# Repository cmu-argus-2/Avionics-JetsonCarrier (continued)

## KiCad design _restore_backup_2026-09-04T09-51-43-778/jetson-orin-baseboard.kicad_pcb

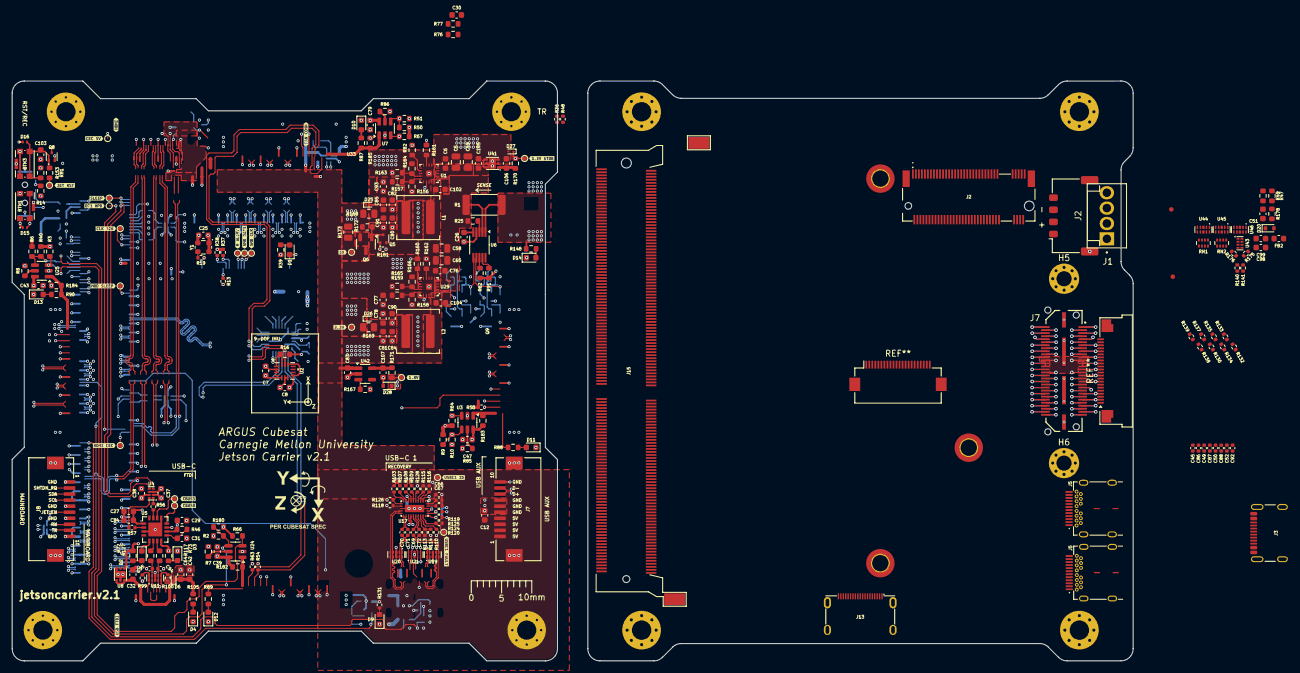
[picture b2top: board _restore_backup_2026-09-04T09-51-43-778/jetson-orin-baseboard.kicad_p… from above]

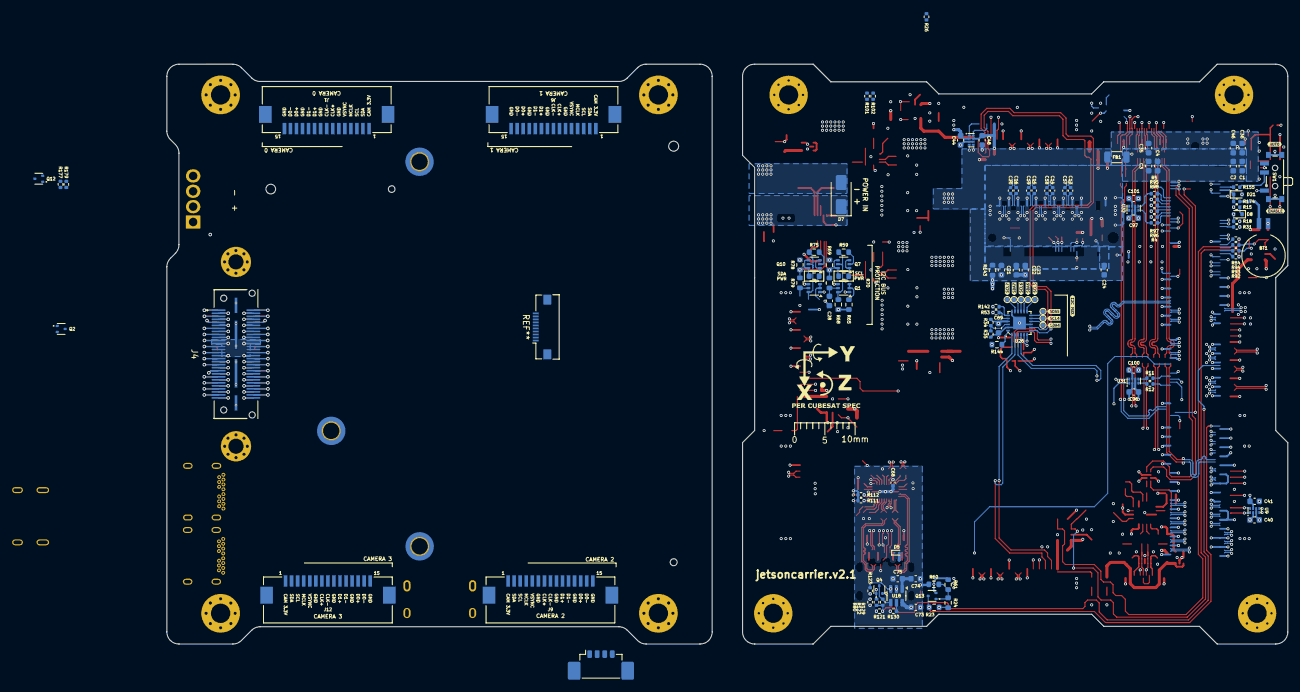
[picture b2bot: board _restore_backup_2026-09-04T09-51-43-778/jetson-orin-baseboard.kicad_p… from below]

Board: 8 copper layers, 90.2 x 95.9 mm, 411 parts (129 on the bottom side), 312 nets.

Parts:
BT1: MS621FE-FL11E
BTN1, BTN3: KMR211NGLFS; SW_Push_1P1T-SH_NO_CK_KMR2xxG
C1, C2, C3, C4, C35, C36, C46, C78, C80, C81, C82, C84, C85, C90, C91: 22uF; C_0603_1608Metric
C5, C58, C59, C65: 22uF; C_0805_2012Metric
C6, C7, C8, C25, C27, C29, C31, C37, C38, C39, C40, C41, C43, C44, C47, C48, C64, C73, C75, C76, C79, C89, C96, C97, C98, C99, C100, C101, C102, C103, C104: 100nF; C_0603_1608Metric
C12, C42, C77, C93, C107: 1uF; C_0603_1608Metric
C13, C14, C15, C16, C17, C18, C19, C20: 220nF; C_0402_1005Metric
C21, C22, C23, C24, C32, C34, C51, C74, C83, C105, C106: 10uF; C_0603_1608Metric
C26: 3300pF; C_0603_1608Metric
C28, C30: 10nF; C_0603_1608Metric
C45, C49, C50, C52, C67, C68, C69, C70, C71, C72, C86, C87, C88, C92: 100nF; C_0402_1005Metric
C66: 10uF; C_0402_1005Metric
C94, C95: 47pF; C_0402_1005Metric
D1, D2, D3, D4, D9, D10, D11, D12, D13, D14: LED_G_0603_LTST-C190GKT; LED_0603_1608Metric
D5, D6, D25: ESD9X5.0ST5G; D_SOD-923
D7: 10V; D_SMA
D8, D20, D21: RB521S30T1G; D_SOD-523
D15, D16: TPD1E0B04; Texas_DPY0002A_0.6x1mm_P0.65mm
D26, D27: ESD9X3.3ST5G; D_SOD-923
D28: ESD1V8WT; D_SOD-523
FB1: 74279221100; L_1206_3216Metric
FB2: BLM21PG221SN1D; L_0603_1608Metric
H1, H2#2, H3#2, H4#2: MountingHole_Pad; MountingHole2
H1#2, H2, H3, H4: MountingHole_Pad; MountingHole_3.2mm_M3_Pad_Via
H5, H6#2: MountingHole_Pad; MountingHole_2.5mm_Pad_Via
H5#2: 9774025151; MountingHole_2.7mm_M2.5_DIN965_Pad_TopBottom
H6, H7: 9774065151; MountingHole_2.7mm_M2.5_DIN965_Pad_TopBottom
J1: 205338-0004; Molex_Pico-Lock_205338-0004_1x04-1MP_P2.00mm_Horizontal
J1#2, J6, J9, J12: 522071560; CON_522071560_MOL
J2: 282834-4; TE_282834-4
J2#2: 1-2199230-6; Bus_M.2_Socket_Key_M_TE_1-2199230-6
J3: USB4105-GF-A; USB_C_Receptacle_GCT_USB4105-xx-A_16P_TopMnt_Horizontal
J4: QTH-030-01-L-D-A; SAMTEC_QSH-030-01-L-D-A
J5, J5#2: 632723300011; USB-C_Receptacle_WE_632723300011
J7, J8: 522711069; CON_522711069_MOL
J7#2: QTH-030-01-L-D-A; SAMTEC-QTH-030-01-L-D-A
J10: 0533980471; Molex_PicoBlade_53398-0471_1x04-1MP_P1.25mm_Vertical
J13: 685119136923; HDMI-Mini-C_Receptacle_WE_685119136923
J15: Bus_DDR4_SODIMM_CUSTOM_Jetson-Orin-H9.2mm-socket; TE_2309413
L1, L2: XGL6030-182MEC; L_Coilcraft_XAL6030-XXX
Q1, Q9: BSS138DWQ-7; SOT-363_SC-70-6
Q2, Q4, Q5, Q8, Q12, Q13: PJE138K; SOT-523
Q6: SSM3J332R; SOT-23-3
Q7, Q10: MBT2222ADW1T1; SOT-363_SC-70-6
R1: 10m; R_2512_6332Metric
R2, R6, R10, R49, R51, R65, R76, R178: 100k; R_0603_1608Metric
R3, R9, R14, R16, R24, R40, R46, R47, R50, R60, R64, R66, R67, R68, R69, R77, R78, R81, R82, R144, R148, R157, R159, R161, R162, R172, R180: 10k; R_0603_1608Metric
R4, R5, R11, R12, R13, R19, R34, R35, R53, R56, R57, R84, R92, R93, R94, R95, R96, R97, R98, R103, R107, R108, R109, R110, R113, R114, R118, R119, R124, R125, R140, R141, R142, R155, R181: 0R; R_0402_1005Metric
R7, R8, R85, R86, R87, R88, R89, R90, R105: 4k7; R_0603_1608Metric
R15: 200R; R_0402_1005Metric
R18, R115, R116, R120, R122, R123, R129: 10k; R_0402_1005Metric
R23, R62, R71, R74, R143, R160, R167, R170, R171, R182, R183, R184, R185: 0R; R_0603_1608Metric
R25: 1k; R_0603_1608Metric
R26, R36, R48, R54, R55, R63, R101, R102, R130, R174, R175, R176, R177, R179: 2k2; R_0402_1005Metric
R31, R80, R126: 200k; R_0402_1005Metric
R37, R38: 47k; R_0402_1005Metric
R39, R72, R73: 3k3; R_0603_1608Metric
R59, R75: 680R; R_0603_1608Metric
R61, R70, R79, R153: 200k; R_0603_1608Metric
R91: 150k; R_0603_1608Metric
R99, R100: 5k1; R_0402_1005Metric
R111, R112, R131: 4k7; R_0402_1005Metric
R117, R127: 27R; R_0603_1608Metric
R121: 1k; R_0402_1005Metric
R128: 887k; R_0402_1005Metric
R132, R133, R134, R135, R136, R137, R138, R139: 499R; R_0402_1005Metric
R156, R158: 220k; R_0603_1608Metric
R163: 110k; R_0603_1608Metric
R164: 15k; R_0603_1608Metric
R165: 90k9; R_0603_1608Metric
R166: 20k; R_0603_1608Metric
R168, R169, R173: 0R; R_0805_2012Metric
RN1, RN2: 4x0R; R_Array_Concave_4x0402
SW1: SW_SPDT; SW_SPDT_PCM12
TP5, TP7, TP8, TP9, TP10, TP11, TP12, TP13, TP14, TP15, TP16, TP17, TP18, TP19, TP20, TP21, TP22, TP23, TP24, TP25, TP26, TP27, TP28, TP29, TP30, TP31: TP_0.75mm_SMD; TP_SMD_0.75mm
U1, U29: TPS56C230; QFN-20-1EP_3x3mm_P0.45mm
U2: BMX160; BMX160_BOS
U3, U7, U18, U24, U25: AP22615A; TSOT-23-6
U4, U9, U31, U32, U33, U43: NTS0102; XSON-8_1x1.95mm_P0.5mm
U5: FT230X; QFN-16-1EP_4x4mm_P0.65mm
U6: ADM1176-1ARMZ-R7; MSOP-10_3x3mm_P0.5mm
U8, U41: NCP730BMT330; WSON-6-1EP_2x2mm_P0.65mm
U11, U19, U20, U21, U44, U45, U46: TPD4E05U06QDQARQ1; USON-10_2.5x1mm_P0.5mm
U17: HD3SS3220RNH; WQFN-30-1EP_4.6x2.6mm_P0.4mm
U26: PI4MSD5V9548AZDEX; VQFN-24-1EP_3.8x3.8x1.0mm_P0.5mm
U42: TPS7A0518P; SOT-23-5
Y1: ECS-327MVATX-2-CN-TR3; Oscillator_SMD_ECS_2520MV_2.5x2mm
kibuzzard-66A2C7D6: G***; kibuzzard-66A2C7D6
kibuzzard-66A2C813: G***; kibuzzard-66A2C813
kibuzzard-66A2D521: G***; kibuzzard-66A2D521
kibuzzard-66A2D898: G***; kibuzzard-66A2D898
kibuzzard-66A2DAF8: G***; kibuzzard-66A2DAF8
kibuzzard-66A2E1AC: G***; kibuzzard-66A2E1AC
kibuzzard-66A2E3EB: G***; kibuzzard-66A2E3EB
kibuzzard-66A2E22A: G***; kibuzzard-66A2E22A
kibuzzard-66A2E36E: G***; kibuzzard-66A2E36E
kibuzzard-66A2E37A: G***; kibuzzard-66A2E37A
kibuzzard-66A2E38A: G***; kibuzzard-66A2E38A
kibuzzard-66A2E142: G***; kibuzzard-66A2E142
kibuzzard-66A2E367: G***; kibuzzard-66A2E367
kibuzzard-66A2E384: G***; kibuzzard-66A2E384
kibuzzard-66A2E572: G***; kibuzzard-66A2E572
kibuzzard-66A2E636: G***; kibuzzard-66A2E636
kibuzzard-66A2E657: G***; kibuzzard-66A2E657
kibuzzard-66A2EA01: G***; kibuzzard-66A2EA01
kibuzzard-66A2EB4E: G***; kibuzzard-66A2EB4E
kibuzzard-66A2EB73: G***; kibuzzard-66A2EB73
kibuzzard-66A33B7D: G***; kibuzzard-66A33B7D
kibuzzard-66A33EAB: G***; kibuzzard-66A33EAB
kibuzzard-66A33F01: G***; kibuzzard-66A33F01
kibuzzard-66A33FD4: G***; kibuzzard-66A33FD4
kibuzzard-66A3387D: G***; kibuzzard-66A3387D
kibuzzard-66A3395A: G***; kibuzzard-66A3395A
kibuzzard-66A3478C: G***; kibuzzard-66A3478C
kibuzzard-66A33739: G***; kibuzzard-66A33739
kibuzzard-66A34183: G***; kibuzzard-66A34183
kibuzzard-66A43634: G***; kibuzzard-66A43634
kibuzzard-66A43694: G***; kibuzzard-66A43694
kibuzzard-67FEBB22: G***; kibuzzard-67FEBB22

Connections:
3V3_STDB: BTN3.1, D21.2 (A), D27.1 (K), R14.2, R18.1, R65.1, R68.1, R69.1, R76.1, R77.1, R78.1, R82.2, R170.1, R181.2, TP23.1
5V_SoM: D25.1 (K), FB1.1, Q6.2 (S), R168.1, R172.1, R173.1
+1V8: C37.1, C40.1, C44.1, C89.2, C96.1, C97.1, D28.1 (K), R3.1, R9.1, R31.1, R34.2, R40.1, R47.1, R50.1, R64.1, R66.1, R67.1, R80.2, R121.1, R123.1, R144.2, R171.1, R180.1, TP24.1, U4.3 (VCC_{A}), U4.6 (OE), U9.3 (VCC_{A}), U9.6 (OE), U26.21 (VCC), U31.3 (VCC_{A}), U31.6 (OE), U32.3 (VCC_{A}), U32.6 (OE), U33.3 (VCC_{A}), U33.6 (OE)
+3V3: C7.1, C8.2, C25.2, C38.1, C39.2, C41.1, C43.2, C47.2, C68.2, C79.2, C98.1, C100.1, C101.1, D26.1 (K), Q2.1 (G), R26.1, R36.1, R37.1, R38.1, R39.1, R48.1, R54.1, R55.1, R63.1, R101.1, R102.1, R111.1, R112.1, R126.2, R143.1, R169.2, R175.1, R176.2, R182.1, R183.1, R184.1, R185.1, TP21.1, U2.5 (VDDIO), U2.8 (VDD), U2.12 (CSB), U3.6 (IN), U4.7 (VCC_{B}), U7.6 (IN), U9.7 (VCC_{B}), U17.8 (VCC33), U24.6 (IN), U25.6 (IN), U31.7 (VCC_{B}), U32.7 (VCC_{B}), U43.3 (VCC_{A}), U43.6 (OE), Y1.1 (EN), Y1.4 (VDD)
+3V3_BUS: J4.21, J4.22, J4.23, J4.24
+5V: C12.2, C48.1, C66.2, C67.2, C73.2, C83.1, FB2.1, J7.1, J7.2, J7.3, J7.4, J10.2, Q6.3 (D), R113.2, R115.2, R116.1, R120.1, R173.2, TP28.1, U17.30 (VDD5), U18.6 (IN), U33.7 (VCC_{B}), U42.1 (VIN)
/CSI/3V3_CAM0: J1#2.1, R89.2, R182.2, U24.1 (OUT)
/CSI/3V3_CAM0_ISET: R7.1, U24.5 (ISET)
/CSI/3V3_CAM1: J6.1, R90.2, R184.2, U25.1 (OUT)
/CSI/3V3_CAM1_ISET: R8.1, U25.5 (ISET)
/CSI/3V3_CAM2: J9.1, R88.2, R183.2, U3.1 (OUT)
/CSI/3V3_CAM2_ISET: R85.1, U3.5 (ISET)
/CSI/3V3_CAM3: J12.1, R87.2, R185.2, U7.1 (OUT)
/CSI/3V3_CAM3_ISET: R86.1, U7.5 (ISET)
/CSI/I2C_MUX_A0: R34.1, R35.2, U26.22 (A0)
/CSI/I2C_MUX_RESET: R144.1, U26.24 (~RESET)
/CSI/I2C_MUX_SCL: R142.2, U26.19 (SCL)
/CSI/I2C_MUX_SDA: R53.1, U26.20 (SDA)
/CSI/MUX_I2C_4_SCL: TP9.1, U26.11 (SC4)
/CSI/MUX_I2C_4_SDA: TP8.1, U26.10 (SD4)
/CSI/MUX_I2C_5_SCL: TP14.1, U26.13 (SC5)
/CSI/MUX_I2C_5_SDA: TP13.1, U26.12 (SD5)
/CSI/MUX_I2C_6_SCL: TP18.1, U26.15 (SC6)
/CSI/MUX_I2C_6_SDA: TP17.1, U26.14 (SD6)
/CSI/MUX_I2C_7_SCL: TP20.1, U26.17 (SC7)
/CSI/MUX_I2C_7_SDA: TP19.1, U26.16 (SD7)
/CSI/SCL_CAM0: J1#2.3, R54.2, U26.2 (SC0)
/CSI/SCL_CAM1: J6.3, R48.2, U26.4 (SC1)
/CSI/SCL_CAM2: J9.3, R26.2, U26.6 (SC2)
/CSI/SCL_CAM3: J12.3, R101.2, U26.8 (SC3)
/CSI/SDA_CAM0: J1#2.2, R63.2, U26.1 (SD0)
/CSI/SDA_CAM1: J6.2, R36.2, U26.3 (SD1)
/CSI/SDA_CAM2: J9.2, R55.2, U26.5 (SD2)
/CSI/SDA_CAM3: J12.2, R102.2, U26.7 (SD3)
/CSI/VSYNC_CAM0_3V3: J1#2.5, U31.1 (B_{2})
/CSI/VSYNC_CAM1_3V3: J6.5, U31.8 (B_{1})
/CSI/VSYNC_CAM2_3V3: J9.5, U32.1 (B_{2})
/CSI/VSYNC_CAM3_3V3: J12.5, U32.8 (B_{1})
/HDMI/5V_HDMI: C51.1, C99.1, D20.1 (K), J13.18 (+5V), R177.2, R179.1, U43.7 (VCC_{B})
/HDMI/HDMI_CEC_5V: J13.14 (CEC), TP5.1, U46.5, U46.6
/HDMI/HDMI_CLK_CONN_N: J13.12 (CK-), RN2.5 (R4.2), U45.1, U45.10
/HDMI/HDMI_CLK_CONN_P: J13.11 (CK+), RN2.6 (R3.2), U45.2, U45.9
/HDMI/HDMI_CLK_N: C92.2, R132.1, RN2.4 (R4.1)
/HDMI/HDMI_CLK_P: C52.2, R133.1, RN2.3 (R3.1)
/HDMI/HDMI_D0_CONN_N: J13.9 (D0-), RN2.7 (R2.2), U45.4, U45.7
/HDMI/HDMI_D0_CONN_P: J13.8 (D0+), RN2.8 (R1.2), U45.5, U45.6
/HDMI/HDMI_D0_N: C88.2, R134.1, RN2.2 (R2.1)
/HDMI/HDMI_D0_P: C50.2, R135.1, RN2.1 (R1.1)
/HDMI/HDMI_D1_CONN_N: J13.6 (D1-), RN1.5 (R4.2), U44.1, U44.10
/HDMI/HDMI_D1_CONN_P: J13.5 (D1+), RN1.6 (R3.2), U44.2, U44.9
/HDMI/HDMI_D1_N: C87.2, R136.1, RN1.4 (R4.1)
/HDMI/HDMI_D1_P: C49.2, R137.1, RN1.3 (R3.1)
/HDMI/HDMI_D2_CONN_N: J13.3 (D2-), RN1.7 (R2.2), U44.4, U44.7
/HDMI/HDMI_D2_CONN_P: J13.2 (D2+), RN1.8 (R1.2), U44.5, U44.6
/HDMI/HDMI_D2_N: C86.2, R138.1, RN1.2 (R2.1)
/HDMI/HDMI_D2_P: C45.2, R139.1, RN1.1 (R1.1)
/HDMI/HDMI_HPD_5V: J13.19 (HPD/HEAC-), R49.2, U46.1, U46.10
/HDMI/HDMI_HPD_5V_R: Q12.1 (G), R49.1, R178.1
/HDMI/HDMI_SCL_3V3: R140.2, R176.1, U43.4 (A_{2})
/HDMI/HDMI_SCL_5V: J13.15 (SCL), R179.2, U43.1 (B_{2}), U46.4, U46.7
/HDMI/HDMI_SDA_3V3: R141.2, R175.2, U43.5 (A_{1})
/HDMI/HDMI_SDA_5V: J13.16 (SDA), R177.1, U43.8 (B_{1}), U46.2, U46.9
/M.2/3V3_M2: C21.1, C22.1, C23.1, C24.1, J2#2.2 (3V3), J2#2.4 (3V3), J2#2.12 (3V3), J2#2.14 (3V3), J2#2.16 (3V3), J2#2.18 (3V3), J2#2.70 (3V3), J2#2.72 (3V3), J2#2.74 (3V3), R143.2
/M.2/32.7KHZ_OUT: R19.2, Y1.3 (OUT)
/M.2/C_PCIE0_TX0_N: C17.2, J2#2.47 (PET0_N)
/M.2/C_PCIE0_TX0_P: C13.2, J2#2.49 (PET0_P)
/M.2/C_PCIE0_TX1_N: C18.1, J2#2.35 (PET1_N)
/M.2/C_PCIE0_TX1_P: C14.1, J2#2.37 (PET1_P)
/M.2/C_PCIE0_TX2_N: C19.1, J2#2.23 (PET2_N)
/M.2/C_PCIE0_TX2_P: C15.1, J2#2.25 (PET2_P)
/M.2/C_PCIE0_TX3_N: C20.2, J2#2.11 (PET3_N)
/M.2/C_PCIE0_TX3_P: C16.1, J2#2.13 (PET3_P)
/M.2/M2_M_SMB_CLK: J2#2.40 (SMB_CLK), TP12.1
/M.2/M2_M_SMB_DATA: J2#2.42 (SMB_DATA), TP11.1
/M.2/M2_M_SUSCLK: J2#2.68 (SUSCLK), R19.1
/M.2/PCIE_WAKE_SEL0: J2#2.54 (~PEWAKE), R13.2
/M.2/~M2_M_ALERT: J2#2.44 (ALERT), TP10.1
/Peripherals/FAN_PWM_5V: J10.4, U33.1 (B_{2})
/Peripherals/FAN_TACH_5V: J10.3, U33.8 (B_{1})
/Peripherals/SHUTDOWN_REQ_MB: D8.2 (A), J8.2, R18.2
/SoM/DEBUG_RXD_1V8: J15.238 (UART2_RXD), U4.4 (A_{2})
/SoM/DEBUG_TXD_1V8: J15.236 (UART2_TXD), U4.5 (A_{1})
/SoM/PMIC_BBAT: D21.1 (K), J15.235 (PMIC_BBAT), R174.1
/SoM/SoM_5V_IN: C1.1, C2.1, C3.1, C4.1, C35.1, C36.1, C46.1, FB1.2, J15.251 (VDD_IN), J15.252 (VDD_IN), J15.253 (VDD_IN), J15.254 (VDD_IN), J15.255 (VDD_IN), J15.256 (VDD_IN), J15.257 (VDD_IN), J15.258 (VDD_IN), J15.259 (VDD_IN), J15.260 (VDD_IN)
/SoM/~FORCE_RECOVERY: BTN1.1, D15.2 (A2), J15.214 (~FORCE_RECOVERY)
/Supply/1V8_LDO: C107.1, R171.2, U42.5 (VOUT)
/Supply/3V3_EN: R160.2, U29.12 (EN)
/Supply/3V3_FB: R165.1, R166.1, U29.14 (FB)
/Supply/3V3_LDO: C106.1, R170.2, U41.1 (V_{OUT})
/Supply/3V3_OUT: C78.1, C81.1, C84.1, C90.1, L2.2, R165.2, R169.1
/Supply/3V3_SW: C104.1, L2.1, U29.6 (SW), U29.19 (SW), U29.20 (SW)
/Supply/5V0_EN: R82.1, U1.12 (EN)
/Supply/5V_FB: R163.2, R164.2, U1.14 (FB)
/Supply/5V_OUT: C80.1, C82.1, C85.1, C91.1, L1.2, R163.1, R168.2
/Supply/5V_SW: C102.1, L1.1, U1.6 (SW), U1.19 (SW), U1.20 (SW)
/Supply/A0: R62.1, U6.8 (A0)
/Supply/A1: R91.1, U6.9 (A1)
/USB3, Recovery/USBC1_ADDR: R113.1, R114.2, U17.22 (ADDR)
/USB3, Recovery/USBC1_CC1: J5#2.A5 (CC1), U17.2 (CC1), U21.1, U21.10
/USB3, Recovery/USBC1_CC2: J5#2.B5 (CC2), U17.1 (CC2), U21.5, U21.6
/USB3, Recovery/USBC1_CONN_TX1_N: C70.1, J5#2.A2 (TX1+), U20.2, U20.9
/USB3, Recovery/USBC1_CONN_TX1_P: C71.1, J5#2.A3 (TX1-), U20.1, U20.10
/USB3, Recovery/USBC1_CONN_TX2_N: C69.1, J5#2.B2 (TX2+), U19.4, U19.7
/USB3, Recovery/USBC1_CONN_TX2_P: C72.1, J5#2.B3 (TX2-), U19.5, U19.6
/USB3, Recovery/USBC1_DIR: R126.1, U17.11 (DIR)
/USB3, Recovery/USBC1_FAULT_N: R120.2, TP27.1, U17.24 (VCONN_FAULT_N)
/USB3, Recovery/USBC1_I2C_SDA: R111.2, R124.2, U17.25 (SDA/OUT1)
/USB3, Recovery/USBC1_ID: Q4.1 (G), R23.1, R24.1, R122.1, TP26.1, U17.27 (ID)
/USB3, Recovery/USBC1_INT: R110.2, U17.23 (INT_N/OUT3)
/USB3, Recovery/USBC1_ISC_SCL: R112.2, R125.2, U17.26 (SCL/OUT2)
/USB3, Recovery/USBC1_ISET: R130.1, U18.5 (ISET)
/USB3, Recovery/USBC1_I_MODE: R116.2, U17.3 (CURRENT_MODE)
/USB3, Recovery/USBC1_PORT: R115.1, U17.4 (PORT)
/USB3, Recovery/USBC1_RX1_N: J5#2.B10 (RX1-), U17.14 (RX1-), U20.5, U20.6
/USB3, Recovery/USBC1_RX1_P: J5#2.B11 (RX1+), U17.15 (RX1+), U20.4, U20.7
/USB3, Recovery/USBC1_RX2_N: J5#2.A10 (RX2-), U17.18 (RX2-), U19.1, U19.10
/USB3, Recovery/USBC1_RX2_P: J5#2.A11 (RX2+), U17.19 (RX2+), U19.2, U19.9
/USB3, Recovery/USBC1_TX1_N: C70.2, U17.16 (TX1-)
/USB3, Recovery/USBC1_TX1_P: C71.2, U17.17 (TX1+)
/USB3, Recovery/USBC1_TX2_N: C69.2, U17.20 (TX2-)
/USB3, Recovery/USBC1_TX2_P: C72.2, U17.21 (TX2+)
/USB3, Recovery/USBC1_VBUS: C74.2, C75.2, D5.1 (K), J5#2.A4 (VBUS), J5#2.A9 (VBUS), J5#2.B4 (VBUS), J5#2.B9 (VBUS), R60.1, R128.1, R131.1, U18.1 (OUT)
/USB3, Recovery/USBC1_VBUS_DET: R128.2, U17.5 (VBUS_DET)
/USB3, Recovery/USBSS1_C_RX_N: R103.2, U17.10 (RX-)
/USB3, Recovery/USBSS1_C_RX_P: R107.2, U17.9 (RX+)
/USB3, Recovery/USBSS1_C_TX_N: R108.2, U17.7 (TX-)
/USB3, Recovery/USBSS1_C_TX_P: R109.2, U17.6 (TX+)
/USB3, Recovery/~USBC1_EN_CC: R119.2, U17.29 (ENn_CC)
/USB3, Recovery/~USBC1_EN_MUX: R118.2, U17.12 (ENn_MUX)
/USB Debug, USB2/FTDI_3V3: C27.2, C29.2, C34.2, R46.2, R72.1, R73.2, U5.1 (V_{CCIO}), U5.8 (3V3_{OUT}), U5.10 (V_{CC}), U8.1 (V_{OUT})
/USB Debug, USB2/FTDI_CBUS0: TP15.1, U5.12 (CBUS0)
/USB Debug, USB2/FTDI_CBUS3: TP16.1, U5.14 (CBUS3)
/USB Debug, USB2/FTDI_LED_RX: D3.1 (K), U5.11 (CBUS1)
/USB Debug, USB2/FTDI_LED_TX: D2.1 (K), U5.5 (CBUS2)
/USB Debug, USB2/USBC3_CC1: J3.A5 (CC1), R99.1, U11.1, U11.10
/USB Debug, USB2/USBC3_CC2: J3.B5 (CC2), R100.1, U11.5, U11.6
/USB Debug, USB2/USBC3_D_N: C94.1, J3.A7 (D-), J3.B7 (D-), R117.1, U11.4, U11.7
/USB Debug, USB2/USBC3_D_P: C95.2, J3.A6 (D+), J3.B6 (D+), R127.1, U11.2, U11.9
/USB Debug, USB2/USBC3_VBUS: C32.2, C42.2, C64.2, D6.1 (K), J3.A4 (VBUS), J3.A9 (VBUS), J3.B4 (VBUS), J3.B9 (VBUS), R105.1, U8.4 (EN), U8.6 (V_{IN})
/USB Debug, USB2/USB_FTDI_N: R117.2, U5.7 (D-)
/USB Debug, USB2/USB_FTDI_P: R127.2, U5.6 (D+)
CAM0_FLG: R66.2, R84.2, U24.3 (FLG)
CAM0_PEN: R2.2, R92.2, R180.2, U24.4 (EN)
CAM1_FLG: R3.2, R93.2, U25.3 (FLG)
CAM1_PEN: R6.2, R40.2, R94.2, U25.4 (EN)
CAM2_FLG: R64.2, R95.2, U3.3 (FLG)
CAM2_PEN: R9.2, R10.2, R96.2, U3.4 (EN)
CAM3_FLG: R67.2, R97.2, U7.3 (FLG)
CAM3_PEN: R50.2, R51.2, R98.2, U7.4 (EN)
CSI0_CLK_N: J1#2.8, J15.10 (CSI0_CLK_N)
CSI0_CLK_P: J1#2.7, J15.12 (CSI0_CLK_P)
CSI0_D0_N: J1#2.14, J15.4 (CSI0_D0_N)
CSI0_D0_P: J1#2.13, J15.6 (CSI0_D0_P)
CSI0_D1_N: J1#2.11, J15.16 (CSI0_D1_N)
CSI0_D1_P: J1#2.10, J15.18 (CSI0_D1_P)
CSI1_CLK_N: J6.8, J15.9 (CSI1_CLK_N)
CSI1_CLK_P: J6.7, J15.11 (CSI1_CLK_P)
CSI1_D0_N: J6.14, J15.3 (CSI1_D0_N)
CSI1_D0_P: J6.13, J15.5 (CSI1_D0_P)
CSI1_D1_N: J6.11, J15.15 (CSI1_D1_N)
CSI1_D1_P: J6.10, J15.17 (CSI1_D1_P)
CSI2_CLK_N: J9.8, J15.28 (CSI2_CLK_N)
CSI2_CLK_P: J9.7, J15.30 (CSI2_CLK_P)
CSI2_D0_N: J9.14, J15.22 (CSI2_D0_N)
CSI2_D0_P: J9.13, J15.24 (CSI2_D0_P)
CSI2_D1_N: J9.11, J15.34 (CSI2_D1_N)
CSI2_D1_P: J9.10, J15.36 (CSI2_D1_P)
CSI3_CLK_N: J12.8, J15.27 (CSI3_CLK_N)
CSI3_CLK_P: J12.7, J15.29 (CSI3_CLK_P)
CSI3_D0_N: J12.14, J15.21 (CSI3_D0_N)
CSI3_D0_P: J12.13, J15.23 (CSI3_D0_P)
CSI3_D1_N: J12.11, J15.33 (CSI3_D1_N)
CSI3_D1_P: J12.10, J15.35 (CSI3_D1_P)
DEBUG_RXD: R56.2, U4.1 (B_{2})
DEBUG_TXD: R57.2, U4.8 (B_{1})
DP1_HDMI_AUX_N: J15.98 (DP1_AUX_N), R141.1
DP1_HDMI_AUX_P: J15.100 (DP1_AUX_P), R140.1
DP1_HPD: J15.96 (DP1_HPD), Q12.3 (D), R47.2, TP22.1
DP1_TXD0_HDMI_TX2_N: C86.1, J15.63 (DP1_TXD0_N)
DP1_TXD0_HDMI_TX2_P: C45.1, J15.65 (DP1_TXD0_P)
DP1_TXD1_HDMI_TX1_N: C87.1, J15.69 (DP1_TXD1_N)
DP1_TXD1_HDMI_TX1_P: C49.1, J15.71 (DP1_TXD1_P)
DP1_TXD2_HDMI_TX0_N: C88.1, J15.75 (DP1_TXD2_N)
DP1_TXD2_HDMI_TX0_P: C50.1, J15.77 (DP1_TXD2_P)
DP1_TXD3_HDMI_TXC_N: C92.1, J15.81 (DP1_TXD3_N)
DP1_TXD3_HDMI_TXC_P: C52.1, J15.83 (DP1_TXD3_P)
FAN_PWM: J15.230 (GPIO14/PWM), U33.4 (A_{2})
FAN_TACH: J15.208 (Fan_Tach/GPIO08), U33.5 (A_{1})
GND: BT1.2 (-), BTN1.2, BTN1.SH, BTN3.SH, C1.2, C2.2, C3.2, C4.2, C5.1, C6.2, C7.2, C8.1, C12.1, C21.2, C22.2, C23.2, C24.2, C25.1, C26.1, C27.1, C28.2, C29.1, C30.2, C31.2, C32.1, C34.1, C35.2, C36.2, C37.2, C38.2, C39.1, C40.2, C41.2, C42.1, C43.1, C44.2, C46.2, C47.1, C48.2, C51.2, C58.2, C59.1, C64.1, C65.2, C66.1, C67.1, C68.1, C73.1, C74.1, C75.1, C76.2, C77.1, C78.2, C79.1, C80.2, C81.2, C82.2, C83.2, C84.2, C85.2, C89.1, C90.2, C91.2, C93.2, C94.2, C95.1, C96.2, C97.2, C98.2, C99.2, C100.2, C101.2, C103.1, C105.2, C106.2, C107.2, D4.1 (K), D5.2 (A), D6.2 (A), D7.2 (A), D9.1 (K), D10.1 (K), D11.1 (K), D12.1 (K), D13.1 (K), D14.1 (K), D15.1 (A1), D16.1 (A1), D25.2 (A), D26.2 (A), D27.2 (A), D28.2 (A), H1.1, H1#2.1 (1_1), H2.1 (1_1), H2#2.1, H3.1 (1_1), H3#2.1, H4.1 (1_1), H4#2.1, H5.1 (1_1), H5#2.1, H6.1, H6#2.1 (1_1), H7.1, J1.3, J1.4, J1.MP (MountPin), J1#2.6, J1#2.9, J1#2.12, J1#2.15, J1#2.MP (MountPin), J2.3, J2.4, J2#2.1 (GND), J2#2.3 (GND), J2#2.9 (GND), J2#2.15 (GND), J2#2.21 (GND), J2#2.27 (GND), J2#2.33 (GND), J2#2.39 (GND), J2#2.45 (GND), J2#2.51 (GND), J2#2.57 (GND), J2#2.71 (GND), J2#2.73 (GND), J2#2.75 (GND), J2#2.MP1 (MP), J2#2.MP2 (MP), J3.A1 (GND), J3.A12 (GND), J3.B1 (GND), J3.B12 (GND), J3.S1 (SHIELD), J4.11, J4.12, J4.13, J4.14, J4.15, J4.16, J4.17, J4.18, J4.19, J4.20, J4.25, J4.26, J4.27, J4.28, J4.35, J4.41, J4.44, J4.47, J4.59, J4.60, J4.SH (Shield), J5#2.A1 (GND), J5#2.A12 (GND), J5#2.B1 (GND), J5#2.B12 (GND), J5#2.SH, J6.6, J6.9, J6.12, J6.15, J6.MP (MountPin), J7.5, J7.6, J7.7, J7.10, J7.MP (MountPin), J8.1, J8.5, J8.7, J8.10, J8.MP (MountPin), J9.6, J9.9, J9.12, J9.15, J9.MP (MountPin), J10.1, J10.MP (MountPin), J12.6, J12.9, J12.12, J12.15, J12.MP (MountPin), J13.1 (D2S), J13.4 (D1S), J13.7 (D0S), J13.10 (CKS), J13.13 (GND), J13.SH, J15.1 (GND), J15.2 (GND), J15.7 (GND), J15.8 (GND), J15.13 (GND), J15.14 (GND), J15.19 (GND), J15.20 (GND), J15.25 (GND), J15.26 (GND), J15.31 (GND), J15.32 (GND), J15.37 (GND), J15.38 (GND), J15.43 (GND), J15.44 (GND), J15.49 (GND), J15.50 (GND), J15.55 (GND), J15.56 (GND), J15.61 (GND), J15.62 (GND), J15.67 (GND), J15.68 (GND), J15.73 (GND), J15.74 (GND), J15.79 (GND), J15.80 (GND), J15.85 (GND), J15.86 (GND), J15.102 (GND), J15.107 (GND), J15.113 (GND), J15.119 (GND), J15.125 (GND), J15.129 (GND), J15.132 (GND), J15.135 (GND), J15.138 (GND), J15.141 (GND), J15.144 (GND), J15.146 (GND), J15.147 (GND), J15.152 (GND), J15.153 (GND), J15.158 (GND), J15.159 (GND), J15.164 (GND), J15.165 (GND), J15.170 (GND), J15.171 (GND), J15.176 (GND), J15.177 (GND), J15.200 (GND), J15.201 (GND), J15.231 (GND), J15.241 (GND), J15.242 (GND), J15.243 (GND), J15.244 (GND), J15.245 (GND), J15.246 (GND), J15.247 (GND), J15.248 (GND), J15.249 (GND), J15.250 (GND), J15.261 (MP), J15.262 (MP), Q1.1 (S2), Q1.4 (S1), Q2.2 (S), Q4.2 (S), Q5.2 (S), Q8.2 (S), Q9.1 (S2), Q9.4 (S1), Q12.2 (S), Q13.2 (S), R2.1, R6.1, R7.2, R8.2, R10.1, R16.1, R35.1, R51.1, R61.2, R62.2, R85.2, R86.2, R91.2, R99.2, R100.2, R114.1, R118.1, R119.1, R130.2, R153.2, R157.1, R159.2, R164.1, R166.2, R178.2, SW1.S4 (SH), U1.7 (PGND), U1.8 (PGND), U1.13 (AGND), U1.18 (PGND), U1.21 (PGND), U2.2 (GND_1), U2.3 (GND_2), U2.6 (GNDIO), U2.7 (GND_3), U3.2 (GND), U4.2 (GND), U5.3 (GND), U5.13 (GND), U5.17 (GND), U6.4 (GND), U7.2 (GND), U8.3 (GND), U8.5 (PG), U8.7 (GND), U9.2 (GND), U11.3, U11.8, U17.13 (GND), U17.28 (GND), U17.31 (GND), U18.2 (GND), U19.3, U19.8, U20.3, U20.8, U21.3, U21.8, U24.2 (GND), U25.2 (GND), U26.9 (GND), U26.18 (A2), U26.23 (A1), U26.25 (EP), U29.7 (PGND), U29.8 (PGND), U29.13 (AGND), U29.18 (PGND), U29.21 (PGND), U31.2 (GND), U32.2 (GND), U33.2 (GND), U41.3 (GND), U41.5 (PG), U41.7 (GND), U42.2 (GND), U43.2 (GND), U44.3, U44.8, U45.3, U45.8, U46.3, U46.8, Y1.2 (GND)
I2C1_SCL: J15.189 (I2C1_SCL), U2.13 (SCX)
I2C1_SDA: J15.191 (I2C1_SDA), U2.14 (SDX)
JETSON_EN: J8.6, SW1.1
JETSON_RST: R81.2, TP31.1
MB_JETSON_RX: J8.8, U9.8 (B_{1})
MB_JETSON_TX: J8.9, U9.1 (B_{2})
MB_SCL: J8.4, Q7.1 (E1), Q7.3 (C2), R71.1
MB_SDA: J8.3, Q10.1 (E1), Q10.3 (C2), R74.1
MCLK_CAM0: J1#2.4, J15.116 (CAM0_MCLK)
MCLK_CAM1: J6.4, J15.122 (CAM1_MCLK)
MCLK_CAM2: J9.4, J15.118 (GPIO01/CLK)
MCLK_CAM3: J12.4, J15.216 (GPIO11/CLK)
unnamed: BT1.1 (+), R174.2
unnamed: D1.2 (A), R39.2
unnamed: D1.1 (K), J2#2.10 (LED)
unnamed: D2.2 (A), R72.2
unnamed: D3.2 (A), R73.1
unnamed: D4.2 (A), R105.2
unnamed: D8.1 (K), R15.2
unnamed: D9.2 (A), R131.2
unnamed: D10.2 (A), R87.1
unnamed: D11.2 (A), R88.1
unnamed: D12.2 (A), R89.1
unnamed: D13.2 (A), R90.1
unnamed: D14.2 (A), R148.2
unnamed: BTN3.2, C103.2, D16.2 (A2), Q8.1 (G), R81.1, R153.1
unnamed: D20.2 (A), FB2.2
unnamed: J15.210 (CLK_32K_OUT), TP7.1
unnamed: J15.114 (CAM0_PWDN), R12.2
unnamed: J15.120 (CAM1_PWDN), R11.1
unnamed: J15.195 (I2S0_DIN), R93.1
unnamed: J15.193 (I2S0_DOUT), R92.1
unnamed: J15.197 (I2S0_FS), R94.1
unnamed: J15.199 (I2S0_SCLK), R84.1
unnamed: J15.222 (I2S1_DIN), R97.1
unnamed: J15.220 (I2S1_DOUT), R96.1
unnamed: J15.224 (I2S1_FS), R98.1
unnamed: J15.226 (I2S1_SCLK), R95.1
unnamed: J15.94 (HDMI_CEC), TP25.1
unnamed: J15.218 (GPIO12/PWM), R4.1
unnamed: J15.228 (GPIO13/PWM), R5.1
unnamed: Q1.6 (D1), Q7.5 (B2), R59.2, R68.2
unnamed: Q1.2 (G2), Q1.3 (D2), R65.2
unnamed: C28.1, Q1.5 (G1), R70.2
unnamed: Q2.3 (D), R132.2, R133.2, R134.2, R135.2, R136.2, R137.2, R138.2, R139.2
unnamed: Q4.3 (D), R129.2, U18.4 (EN)
unnamed: Q5.3 (D), Q6.1 (G), R172.2
unnamed: Q7.2 (B1), R59.1
unnamed: Q9.2 (G2), Q9.3 (D2), R76.2
unnamed: C30.1, Q9.5 (G1), R79.2
unnamed: Q10.2 (B1), R75.1
unnamed: Q9.6 (D1), Q10.5 (B2), R75.2, R77.2
unnamed: Q13.1 (G), R24.2, R60.2, R61.1
unnamed: R14.1, SW1.3
unnamed: R155.1, SW1.2
unnamed: C102.2, U1.1 (BST)
unnamed: R156.2, R157.2, U1.15 (MODE)
unnamed: R161.2, U1.9 (PG)
unnamed: C93.1, R156.1, R161.1, U1.17 (V_{CC})
unnamed: R16.2, U2.1 (SDO)
unnamed: R57.1, U5.2 (RXD)
unnamed: R56.1, U5.15 (TXD)
unnamed: C31.1, R46.1, U5.9 (~RESET)
unnamed: R25.2, U6.3 (ON)
unnamed: C26.2, U6.5 (TIMER)
unnamed: C104.2, U29.1 (BST)
unnamed: R158.1, R159.1, U29.15 (MODE)
unnamed: R162.2, U29.9 (PG)
unnamed: C77.2, R158.2, R162.1, U29.17 (V_{CC})
unnamed: R167.2, U42.3 (EN)
PCIE0_CLKREQ*: J2#2.52 (~CLKREQ), J15.180 (~PCIE0_CLKREQ), R38.2
PCIE0_CLK_N: J2#2.53 (REFCLK_N), J15.160 (PCIE0_CLK_N)
PCIE0_CLK_P: J2#2.55 (REFCLK_P), J15.162 (PCIE0_CLK_P)
PCIE0_RST*: J2#2.50 (~PERST), J15.181 (~PCIE0_RST), R37.2
PCIE0_RX0_N: J2#2.41 (PER0_N), J15.131 (PCIE0_RX0_N)
PCIE0_RX0_P: J2#2.43 (PER0_P), J15.133 (PCIE0_RX0_P)
PCIE0_RX1_N: J2#2.29 (PER1_N), J15.137 (PCIE0_RX1_N)
PCIE0_RX1_P: J2#2.31 (PER1_P), J15.139 (PCIE0_RX1_P)
PCIE0_RX2_N: J2#2.17 (PER2_N), J15.149 (PCIE0_RX2_N)
PCIE0_RX2_P: J2#2.19 (PER2_P), J15.151 (PCIE0_RX2_P)
PCIE0_RX3_N: J2#2.5 (PER3_N), J15.155 (PCIE0_RX3_N)
PCIE0_RX3_P: J2#2.7 (PER3_P), J15.157 (PCIE0_RX3_P)
PCIE0_TX0_N: C17.1, J15.134 (PCIE0_TX0_N)
PCIE0_TX0_P: C13.1, J15.136 (PCIE0_TX0_P)
PCIE0_TX1_N: C18.2, J15.140 (PCIE0_TX1_N)
PCIE0_TX1_P: C14.2, J15.142 (PCIE0_TX1_P)
PCIE0_TX2_N: C19.2, J15.148 (PCIE0_TX2_N)
PCIE0_TX2_P: C15.2, J15.150 (PCIE0_TX2_P)
PCIE0_TX3_N: C20.1, J15.154 (PCIE0_TX3_N)
PCIE0_TX3_P: C16.2, J15.156 (PCIE0_TX3_P)
PCIE_WAKE*: J15.179 (~PCIE_WAKE), R13.1
POWER_EN: J15.237 (POWER_EN), R155.2
PWR_SCL: Q7.4 (E2), Q7.6 (C1), R69.2, R70.1, R71.2, U6.6 (SCL)
PWR_SDA: Q10.4 (E2), Q10.6 (C1), R74.2, R78.2, R79.1, U6.7 (SDA)
SCL_CAM: J15.213 (CAM_I2C_SCL), R142.1
SDA_CAM: J15.215 (CAM_I2C_SDA), R53.2
SLEEP/~WAKE: J15.240 (SLEEP/~WAKE), TP29.1
SYS_SCL: J15.185 (I2C0_SCL), R125.1
SYS_SDA: J15.187 (I2C0_SDA), R124.1
UART1_RXD: J15.205 (UART1_RXD), U9.5 (A_{1})
UART1_TXD: J15.203 (UART1_TXD), U9.4 (A_{2})
USB0_D_N: J5#2.A7 (D-), J5#2.B7 (D-), J15.109 (USB0_D_N), U21.4, U21.7
USB0_D_P: J5#2.A6 (D+), J5#2.B6 (D+), J15.111 (USB0_D_P), U21.2, U21.9
USB1_D_N: J7.9, J15.115 (USB1_D_N)
USB1_D_P: J7.8, J15.117 (USB1_D_P)
USBC1_FLG: J15.128 (GPIO05), R123.2, U18.3 (FLG)
USBC1_PEN: J15.127 (GPIO04), R121.2, R122.2, R129.1
USBSS2_RX_N: J15.51 (USBSS2_RX_N), R103.1
USBSS2_RX_P: J15.53 (USBSS2_RX_P), R107.1
USBSS2_TX_N: J15.57 (USBSS2_TX_N), R108.1
USBSS2_TX_P: J15.59 (USBSS2_TX_P), R109.1
USB_FLASH_ID: J15.87 (USB_VBUS_EN0/GPIO00), Q13.3 (D), R23.2
VBATT: D7.1 (K), J1.1, J1.2, J2.1, J2.2, J4.1, J4.2, J4.3, J4.4, J4.5, J4.6, J4.7, J4.8, J4.9, J4.10, R1.2, R148.1, U6.1 (VCC)
VCC: C5.2, C6.1, C58.1, C59.2, C65.1, C76.1, C105.1, R1.1, R25.1, U1.2 (V_{IN}), U1.3 (V_{IN}), U1.4 (V_{IN}), U1.5 (V_{IN}), U6.2 (SENSE), U29.2 (V_{IN}), U29.3 (V_{IN}), U29.4 (V_{IN}), U29.5 (V_{IN}), U41.4 (EN), U41.6 (V_{IN})
VSYNC_CAM0: R12.1, U31.4 (A_{2})
VSYNC_CAM1: R11.2, U31.5 (A_{1})
VSYNC_CAM2: R4.2, U32.4 (A_{2})
VSYNC_CAM3: R5.2, U32.5 (A_{1})
~MOD_SLEEP: J15.178 (~MOD_SLEEP), TP30.1
~RESET: J15.239 (~SYS_RESET), Q5.1 (G), Q8.3 (D), R160.1, R167.1, R181.1
~SHUTDOWN_REQ: J15.233 (~SHUTDOWN_REQ), R15.1
~USBC0_INT: J15.211 (GPIO09/AUD_MCLK), R31.2
~USBC1_INT: J15.212 (GPIO10), R80.1, R110.1

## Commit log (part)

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2025-03-10 v2.0 Schematic updates
2025-04-16 v2.0 Layout completed. Exported BOM and STEP files
2025-05-05 Fix connector name
2025-06-18 v2.1 Updates
2026-01-21 Local Stash
2026-02-09 Local Stash 2
